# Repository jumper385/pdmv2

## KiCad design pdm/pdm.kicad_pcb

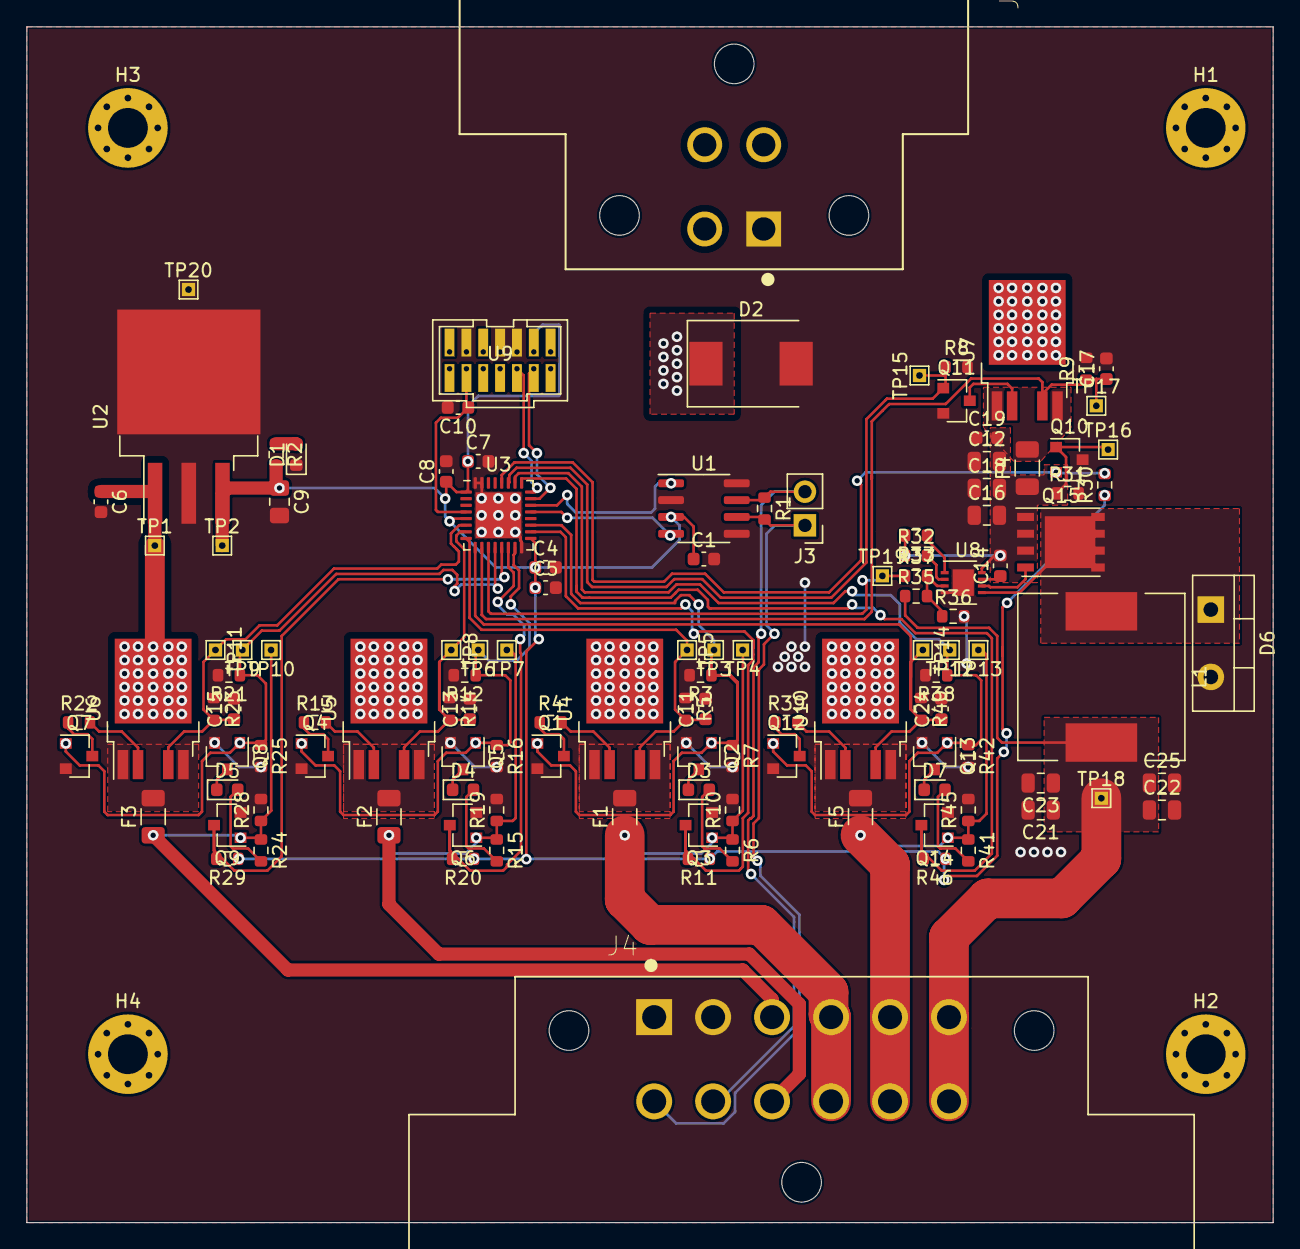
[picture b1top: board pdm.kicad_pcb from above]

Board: 4 copper layers, 94.0 x 90.2 mm, 126 parts (0 on the bottom side), 61 nets.

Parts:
C1, C4, C6, C7, C8: 0.1uF; C_0603_1608Metric
C5, C11, C13, C14, C15, C17, C24: 1uF; C_0603_1608Metric
C9: 10uF; C_0805_2012Metric_Pad1.18x1.45mm_HandSolder
C10: 0.1pF; C_0603_1608Metric
C12, C16, C18, C23: 15uF; C_0805_2012Metric
C19: 0.47uF; C_0603_1608Metric
C21, C22, C25: N/C; C_0805_2012Metric
D1, D3, D4, D5, D7: LED; LED_0603_1608Metric
D2: D; D_SMC
D6: VS-20TQ045-M3; TO-220-2_Vertical
F1, F2, F3, F4, F5: Fuse; Fuse_1206_3216Metric
H1, H2, H3, H4: MountingHole; MountingHole_3mm_Pad_Via
J1: Conn_01x04_Male; TE_DT13-4P
J3: Conn_01x02_Male; PinHeader_1x02_P2.54mm_Vertical
J4: Conn_01x12_Male; TE_DT13-12PB-B016
L1: 3.3uH; L_12x12mm_H8mm
Q1, Q2, Q3, Q4, Q5, Q6, Q7, Q8, Q9, Q10, Q11, Q12, Q13, Q14: 2N7002E; SOT-23
Q15: Si7141DP; PowerPAK_SO-8_Single
R1, R2: 120R; R_0603_1608Metric
R3, R4, R7, R8, R10, R11, R12, R13, R16, R19, R20, R21, R22, R25, R28, R29, R30, R31, R38, R39, R42, R45, R46: 10k; R_0603_1608Metric
R5, R14, R23, R40: 1K5; R_0603_1608Metric
R6, R15, R24, R41: 850; R_0603_1608Metric
R9: 1k; R_0603_1608Metric
R32: 221k; R_0603_1608Metric
R33: 4.12k; R_0603_1608Metric
R35: 40k; R_0603_1608Metric
R36: 4.7k; R_0603_1608Metric
R37: 7.5k; R_0603_1608Metric
TP1, TP2, TP20: TestPoint_Probe; TestPoint_THTPad_1.0x1.0mm_Drill0.5mm
TP3, TP4, TP5, TP6, TP7, TP8, TP9, TP10, TP11, TP12, TP13, TP14, TP15, TP16, TP17, TP18, TP19: TestPoint; TestPoint_THTPad_1.0x1.0mm_Drill0.5mm
U1: SN65HVD233; SOIC-8_3.9x4.9mm_P1.27mm
U2: LM2937xS; TO-263-3_TabPin2
U3: STM32L432KCUx; QFN-32-1EP_5x5mm_P0.5mm_EP3.45x3.45mm
U4, U5, U6, U7, U10: BTS443P; TO-252-4
U8: LM5085; WSON-8-1EP_3x3mm_P0.5mm_EP1.6x2.0mm
U9: STLINK_V3; STM32_Programmer

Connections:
+3V3: C1.1, C4.1, C5.1, C7.1, C8.1, C9.1, R2.2, R11.1, R20.1, R29.1, R30.1, R46.1, TP2.1, U1.3, U2.3, U3.1, U3.5, U3.17, U9.3
+12V: C6.1, D2.1, J1.2, J1.3, J1.4, TP1.1, U2.1, U4.3, U5.3, U6.3, U7.3, U10.3
/DAC2: R37.1, TP19.1, U3.11
/NRST: C10.1, U3.4, U9.12
/SWCLK: U3.24, U9.6
/SWDIO: U3.23, U9.4
/_N: J3.1, J4.12, R1.2, U1.6
/_P: J3.2, J4.11, R1.1, U1.7
/act1: Q4.1, Q5.1, R12.1, R16.1, TP6.1, U3.15
/act2: Q7.1, Q8.1, R21.1, R25.1, TP9.1, U3.12
/act3: Q1.1, Q2.1, R3.1, R7.1, TP3.1, U3.19
/act4: Q12.1, Q13.1, R38.1, R42.1, TP12.1, U3.26
/act5: Q11.1, R8.1, TP15.1, U3.27
/canrx: U1.4, U3.21
/cantx: U1.1, U3.22
/fuse1: Q6.3, R20.2, U3.14
/fuse2: Q9.3, R29.2, U3.13
/fuse3: Q3.3, R11.2, U3.18
/fuse4: Q14.3, R46.2, U3.25
/fuse5: Q10.2, R30.2, U3.28
/fuse_block/out-unfused: F2.2, U5.1, U5.5
/sense1: C13.1, R14.2, TP8.1, U3.7, U5.4
/sense2: C15.1, R23.2, TP11.1, U3.6, U6.4
/sense3: C11.1, R5.2, TP5.1, U3.8, U4.4
/sense4: C24.1, R40.2, TP14.1, U3.9, U10.4
/sense5: C17.1, R9.1, TP17.1, U3.10, U7.4
/sheet5F955EDF/out-unfused: F3.2, U6.1, U6.5
/sheet5F955F69/out-unfused: F1.2, U4.1, U4.5
/sheet60D2AFEF/out-unfused: F5.2, U10.1, U10.5
/sheet60F4D953/BUCK_FUSE_OUT: C12.2, C14.2, C16.2, C18.2, C19.2, F4.1, Q10.1, Q15.1, Q15.2, Q15.3, R31.1, R32.1, R33.2, TP16.1, U8.8
/sheet60F4D953/PMOS_OUT: D6.1, L1.1, Q15.5, U8.5
/vout1: F2.1, J4.10, Q6.1, R15.1, R19.1, TP7.1
/vout2: F3.1, J4.3, Q9.1, R24.1, R28.1, TP10.1
/vout3: F1.1, J4.4, J4.9, Q3.1, R6.1, R10.1, TP4.1
/vout4: F5.1, J4.5, J4.8, Q14.1, R41.1, R45.1, TP13.1
/vout5: C21.1, C22.1, C23.1, C25.1, J4.6, J4.7, L1.2, R35.1, TP18.1
GND: C1.2, C4.2, C5.2, C6.2, C7.2, C8.2, C9.2, C10.2, C11.2, C12.1, C13.2, C15.2, C16.1, C17.2, C18.1, C19.1, C21.2, C22.2, C23.2, C24.2, C25.2, D1.1, D2.2, D6.2, J1.1, J4.1, J4.2, Q1.2, Q2.2, Q3.2, Q4.2, Q5.2, Q6.2, Q7.2, Q8.2, Q9.2, Q10.3, Q11.2, Q12.2, Q13.2, Q14.2, R3.2, R5.1, R7.2, R8.2, R9.2, R10.2, R12.2, R14.1, R16.2, R19.2, R21.2, R23.1, R25.2, R28.2, R31.2, R36.2, R38.2, R40.1, R42.2, R45.2, TP20.1, U1.2, U1.5, U1.8, U2.2, U3.16, U3.31, U3.32, U3.33, U8.4, U8.9, U9.5, U9.7, U9.11
unnamed: C14.1, U8.7
unnamed: D1.2, R2.1
unnamed: D3.1, Q2.3
unnamed: D3.2, R6.2
unnamed: D4.1, Q5.3
unnamed: D4.2, R15.2
unnamed: D5.1, Q8.3
unnamed: D5.2, R24.2
unnamed: D7.1, Q13.3
unnamed: D7.2, R41.2
unnamed: F4.2, U7.1, U7.5
unnamed: Q1.3, R4.1
unnamed: Q4.3, R13.1
unnamed: Q7.3, R22.1
unnamed: Q11.3, U7.2
unnamed: Q12.3, R39.1
unnamed: Q15.4, U8.6
unnamed: R4.2, U4.2
unnamed: R13.2, U5.2
unnamed: R22.2, U6.2
unnamed: R32.2, U8.2
unnamed: R33.1, U8.1
unnamed: R35.2, R36.1, R37.2, U8.3
unnamed: R39.2, U10.2

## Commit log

2020-12-30 changed to molex headers
2020-12-30 added photo render
2021-01-05 rotated molex
2021-01-12 added connector changes
2021-01-16 changed layout with two plugs
2021-01-16 added placeholder oscillator
2021-01-16 added mount and moved 12 pin
2021-01-16 added pin mappings
2021-01-16 added mounting holes again
2021-01-16 fixed labelling
2021-01-16 added exports
2021-01-17 added exports folder
2021-01-17 fixed issues #3 & #5
2021-01-17 added block labels as per issue #4
2021-01-17 added high current labels for issue #4
2021-01-17 added mounting holes as per issue #2
2021-01-17 added pepe as per issue #1
2021-01-18 added pdm
2021-01-26 fixed issues #7 #8 #9 #10
2021-01-26 moved led's to side of mosfet for issue #9
2021-01-26 added more vias to LDR #10 & channged to pin female #8
2021-01-26 fixed DRC's
2021-01-26 added nrst conenction
2021-01-26 added N/C to headers
2021-01-26 added some exports
2021-01-26 added pdm step export
2021-01-26 added digikey BoM
2021-02-02 added fixes for issue #11 #12 & #13
2021-02-04 removed 3v3 w/ gnd on out
2021-02-05 added phatter tracks
2021-02-06 Fixed LED Work
2021-02-12 changed oscilltor and exposed themral pads
2021-05-12 major redesign - hc switching output
2021-05-19 fixed schematic
2021-06-12 new layout
2021-06-20 finished layout v2
2021-06-20 adding BoM
2021-06-20 completed BoM
2021-06-27 polished layout
2021-06-28 final updates + gerbers
2021-07-27 general changes
2021-09-30 changed parts layout
2021-10-02 completed routing
